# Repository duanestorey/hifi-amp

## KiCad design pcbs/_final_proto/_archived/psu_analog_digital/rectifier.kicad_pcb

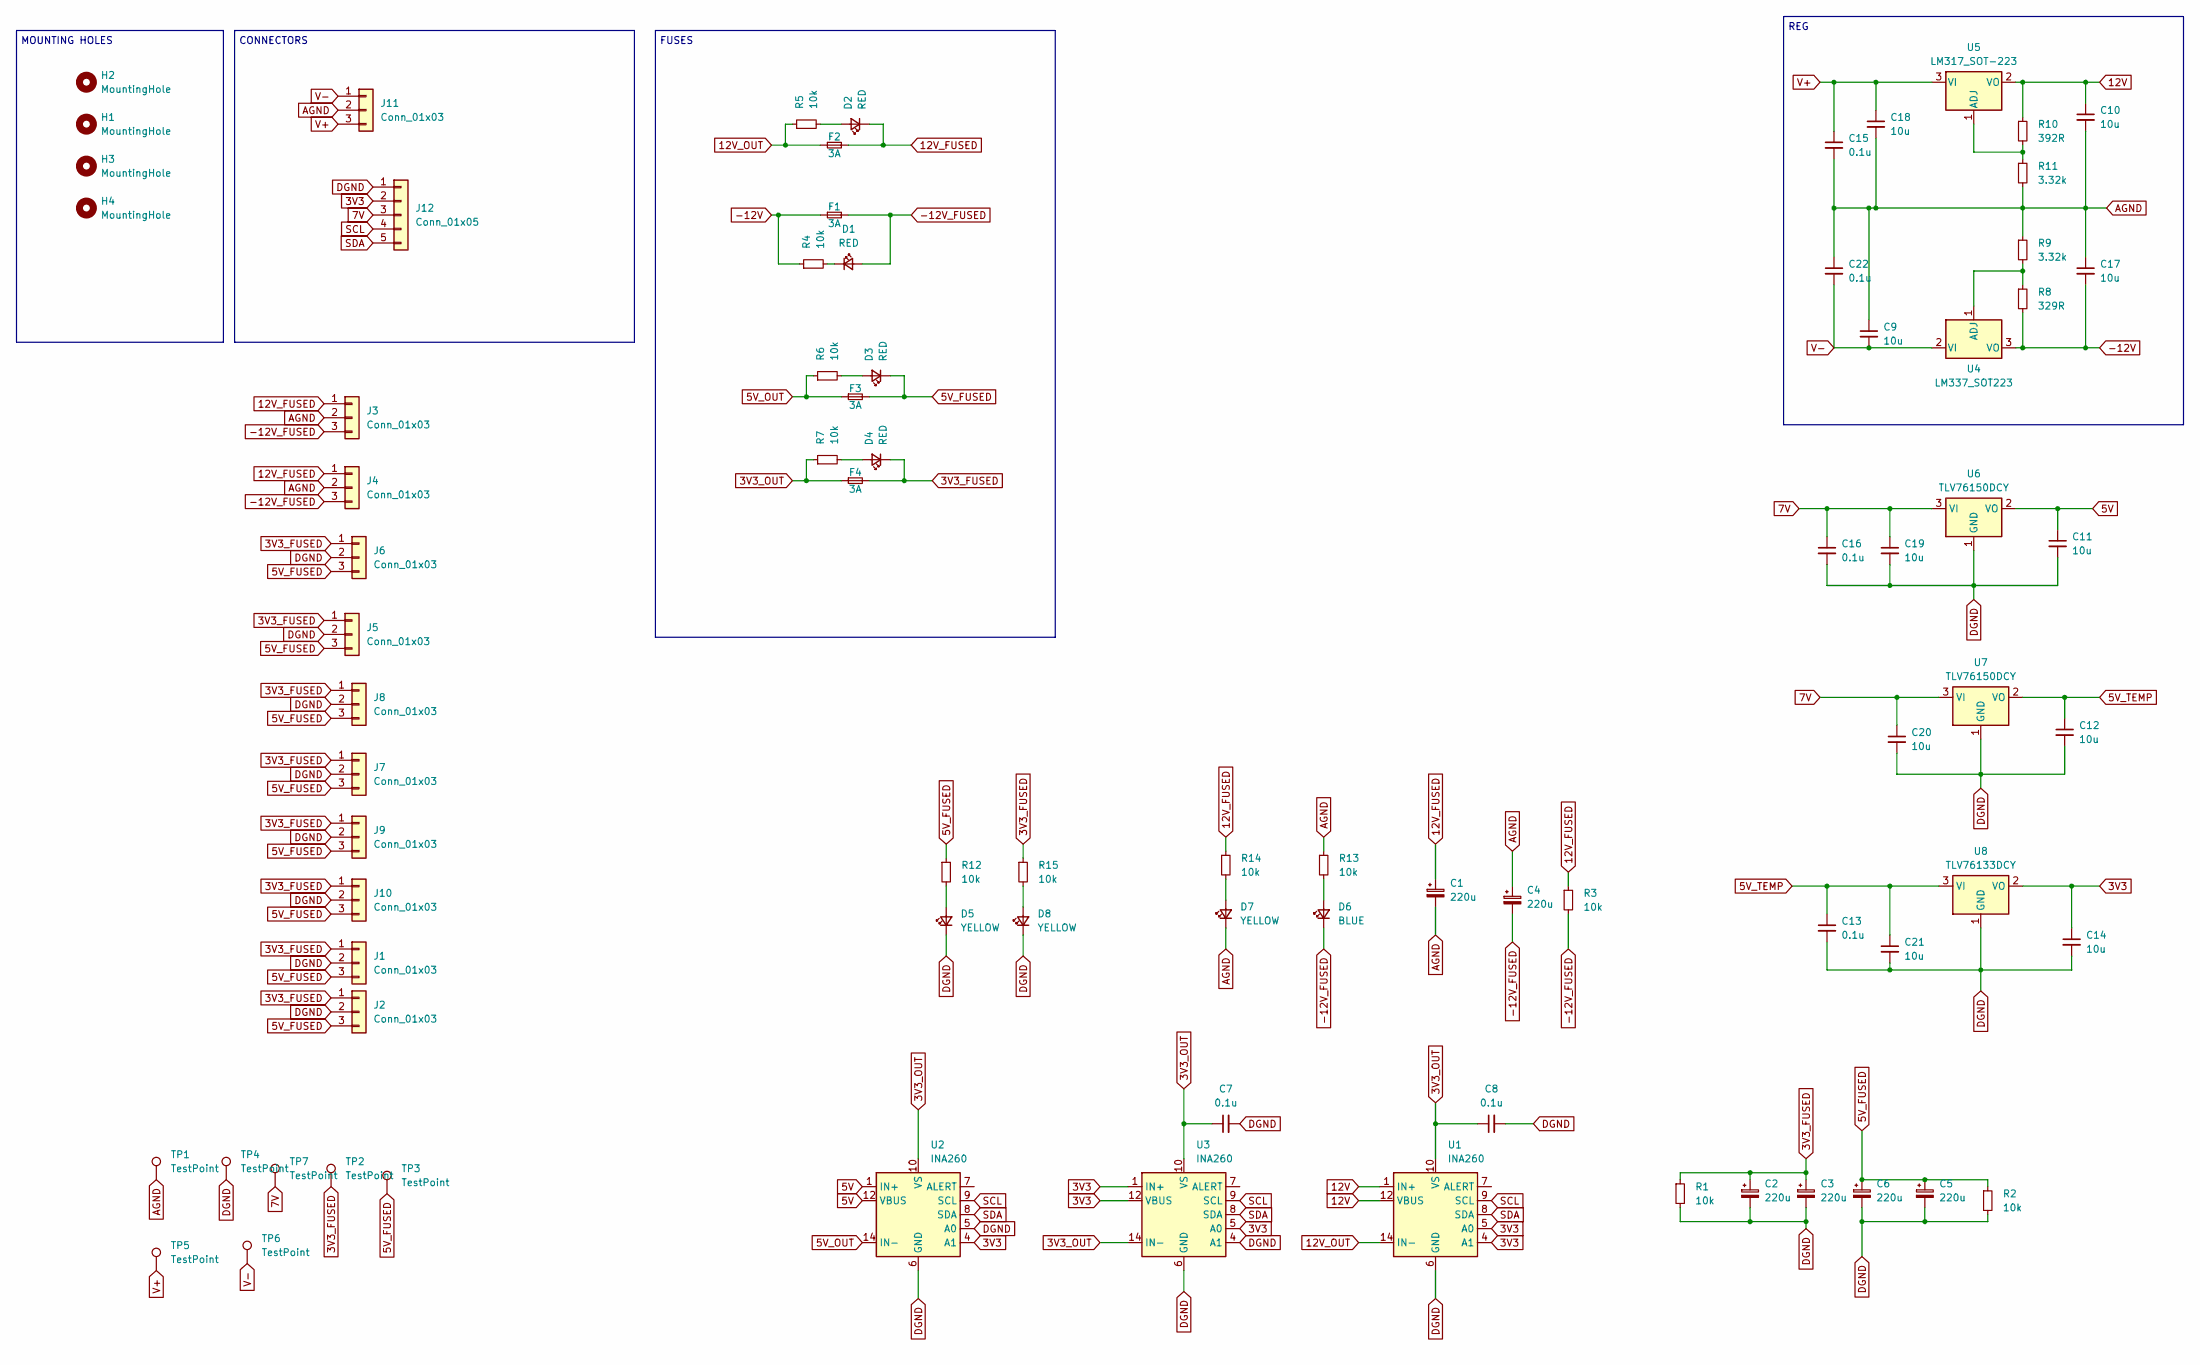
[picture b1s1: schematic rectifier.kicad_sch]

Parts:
C1, C2, C3, C4, C5, C6: 220u; CP_Radial_D6.3mm_P2.50mm
C7, C8, C13, C15, C16, C22: 0.1u; C_0805_2012Metric_Pad1.18x1.45mm_HandSolder
C9, C10, C11, C12, C14, C17, C18, C19, C20, C21: 10u; C_1206_3216Metric_Pad1.33x1.80mm_HandSolder
D1, D2, D3, D4: RED; LED_0805_2012Metric_Pad1.15x1.40mm_HandSolder
D5, D7, D8: YELLOW; LED_0805_2012Metric_Pad1.15x1.40mm_HandSolder
D6: BLUE; LED_0805_2012Metric_Pad1.15x1.40mm_HandSolder
F1, F2, F3, F4: 3A; Fuse_1812_AliExpress
H1, H2, H3, H4: MountingHole; MountingHole_3.2mm_M3_DIN965_Pad_TopBottom
J1, J2, J3, J4, J5, J6, J7, J8, J9, J10, J11: Conn_01x03; JST_PH_B3B-PH-K_1x03_P2.00mm_Vertical
J12: Conn_01x05; JST_PH_B5B-PH-K_1x05_P2.00mm_Vertical
R1, R2, R3, R4, R5, R6, R7, R12, R13, R14, R15: 10k; R_0805_2012Metric_Pad1.20x1.40mm_HandSolder; Mouser 603-SR2512JK-7W10RL
R8: 329R; R_0805_2012Metric_Pad1.20x1.40mm_HandSolder; Mouser 652-CR0805FX-3920ELF
R9, R11: 3.32k; R_0805_2012Metric_Pad1.20x1.40mm_HandSolder; Mouser AC0805FR-073K32L
R10: 392R; R_0805_2012Metric_Pad1.20x1.40mm_HandSolder; Mouser 652-CR0805FX-3920ELF
TP1, TP2, TP3, TP4, TP5, TP6, TP7: TestPoint; TestPoint_THTPad_1.5x1.5mm_Drill0.7mm
U1, U2, U3: INA260; TSSOP-16_4.4x5mm_P0.65mm
U4: LM337_SOT223; SOT-223-3_TabPin2
U5: LM317_SOT-223; SOT-223-3_TabPin2
U6, U7: TLV76150DCY; SOT-223-3_TabPin2
U8: TLV76133DCY; SOT-223-3_TabPin2

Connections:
3V3: C14.1, J12.2, U1.4 (A1), U1.5 (A0), U2.4 (A1), U3.1 (IN+), U3.2 (IN+), U3.3 (IN+), U3.5 (A0), U3.12 (VBUS), U8.2 (VO)
3V3_FUSED: C2.1, C3.1, D4.1 (K), F4.2, J1.1, J2.1, J5.1, J6.1, J7.1, J8.1, J9.1, J10.1, R1.1, R15.1, TP2.1
3V3_OUT: C7.1, C8.1, F4.1, R7.1, U1.10 (VS), U2.10 (VS), U3.10 (VS), U3.14 (IN-), U3.15 (IN-), U3.16 (IN-)
5V: C11.1, U2.1 (IN+), U2.2 (IN+), U2.3 (IN+), U2.12 (VBUS), U6.2 (VO)
5V_FUSED: C5.1, C6.1, D3.1 (K), F3.2, J1.3, J2.3, J5.3, J6.3, J7.3, J8.3, J9.3, J10.3, R2.1, R12.1, TP3.1
5V_OUT: F3.1, R6.1, U2.14 (IN-), U2.15 (IN-), U2.16 (IN-)
5V_TEMP: C12.1, C13.1, C21.1, U7.2 (VO), U8.3 (VI)
7V: C16.1, C19.1, C20.1, J12.3, TP7.1, U6.3 (VI), U7.3 (VI)
12V: C10.1, R10.1, U1.1 (IN+), U1.2 (IN+), U1.3 (IN+), U1.12 (VBUS), U5.2 (VO)
12V_FUSED: C1.1, D2.1 (K), F2.2, J3.1, J4.1, R3.1, R14.1
12V_OUT: F2.1, R5.1, U1.14 (IN-), U1.15 (IN-), U1.16 (IN-)
-12V: C17.2, F1.1, R4.1, R8.2, U4.3 (VO)
-12V_FUSED: C4.2, D1.2 (A), D6.1 (K), F1.2, J3.3, J4.3, R3.2
AGND: C1.2, C4.1, C9.1, C10.2, C15.2, C17.1, C18.2, C22.1, D7.1 (K), J3.2, J4.2, J11.2, R9.1, R11.2, R13.1, TP1.1
DGND: C2.2, C3.2, C5.2, C6.2, C7.2, C8.2, C11.2, C12.2, C13.2, C14.2, C16.2, C19.2, C20.2, C21.2, D5.1 (K), D8.1 (K), J1.2, J2.2, J5.2, J6.2, J7.2, J8.2, J9.2, J10.2, J12.1, R1.2, R2.2, TP4.1, U1.6 (GND), U1.11 (GND), U2.5 (A0), U2.6 (GND), U2.11 (GND), U3.4 (A1), U3.6 (GND), U3.11 (GND), U6.1 (GND), U7.1 (GND), U8.1 (GND)
unnamed: D1.1 (K), R4.2
unnamed: D2.2 (A), R5.2
unnamed: D3.2 (A), R6.2
unnamed: D4.2 (A), R7.2
unnamed: D5.2 (A), R12.2
unnamed: D6.2 (A), R13.2
unnamed: D7.2 (A), R14.2
unnamed: D8.2 (A), R15.2
unnamed: R8.1, R9.2, U4.1 (ADJ)
unnamed: R10.2, R11.1, U5.1 (ADJ)
SCL: J12.4, U1.9 (SCL), U2.9 (SCL), U3.9 (SCL)
SDA: J12.5, U1.8 (SDA), U2.8 (SDA), U3.8 (SDA)
V+: C15.1, C18.1, J11.3, TP5.1, U5.3 (VI)
V-: C9.2, C22.2, J11.1, TP6.1, U4.2 (VI)

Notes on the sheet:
MOUNTING HOLES
REG
CONNECTORS
FUSES

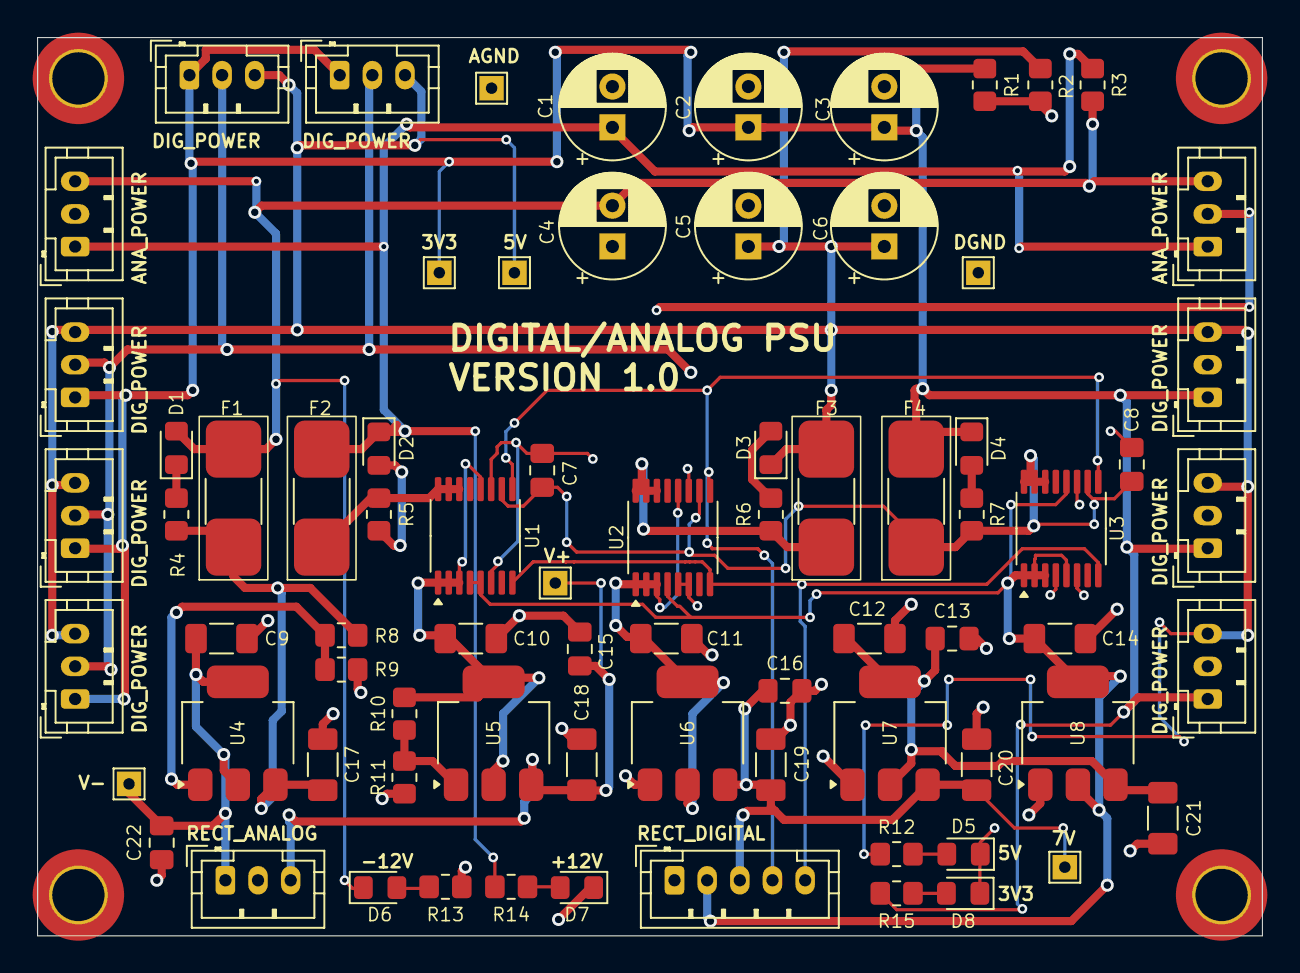
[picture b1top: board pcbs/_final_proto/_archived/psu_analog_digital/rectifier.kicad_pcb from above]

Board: 2 copper layers, 75.0 x 55.0 mm, 80 parts (0 on the bottom side), 29 nets.

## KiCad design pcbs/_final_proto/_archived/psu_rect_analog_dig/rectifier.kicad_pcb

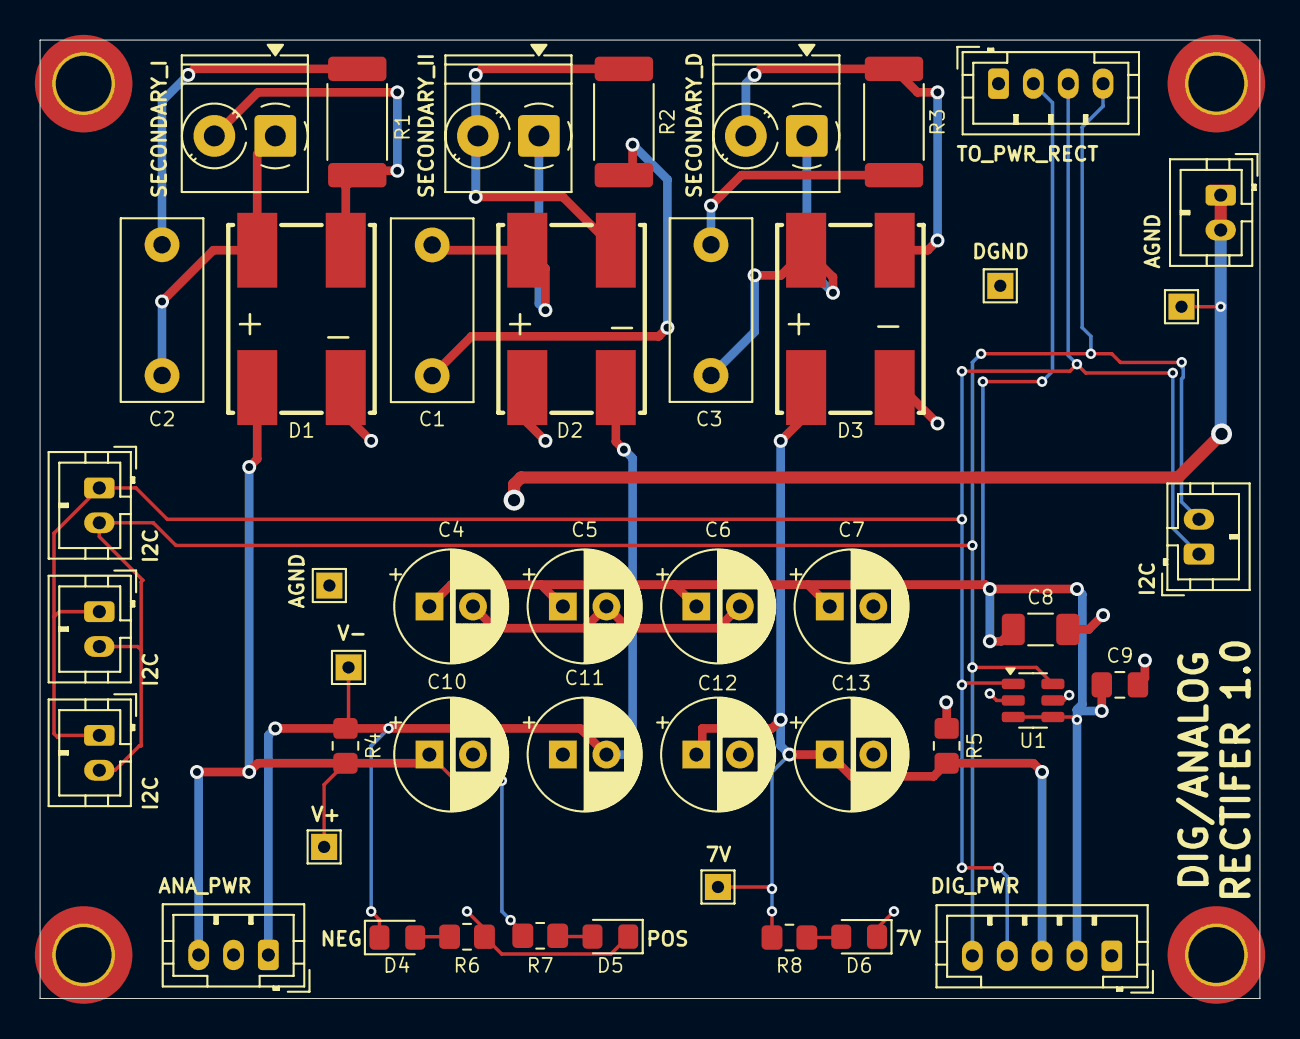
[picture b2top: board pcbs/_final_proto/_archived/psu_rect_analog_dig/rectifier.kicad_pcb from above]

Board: 2 copper layers, 70.0 x 55.0 mm, 49 parts (0 on the bottom side), 20 nets.

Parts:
C1, C2, C3: 100N; C_Rect_L10.3mm_W4.5mm_P7.50mm_MKS4
C4, C5, C6, C7, C10, C11, C12, C13: 220u; CP_Radial_D6.3mm_P2.50mm
C8: 10u; C_1206_3216Metric_Pad1.33x1.80mm_HandSolder
C9: 0.1u; C_0805_2012Metric_Pad1.18x1.45mm_HandSolder
D1, D2, D3: CD-DF406SL; Z4-D_4P-L10.5-W8.1-P5.08-TL
D4: BLUE; LED_0805_2012Metric_Pad1.15x1.40mm_HandSolder
D5, D6: YELLOW; LED_0805_2012Metric_Pad1.15x1.40mm_HandSolder
H1, H2, H3, H4: MountingHole; MountingHole_3.2mm_M3_DIN965_Pad_TopBottom
J1: Conn_01x04; JST_PH_B4B-PH-K_1x04_P2.00mm_Vertical
J2, J3, J4: Conn_01x02; TerminalBlock_Phoenix_PT-1,5-2-3.5-H_1x02_P3.50mm_Horizontal
J5, J6, J9, J10, J11: Conn_01x02; JST_PH_B2B-PH-K_1x02_P2.00mm_Vertical
J7: Conn_01x03; JST_PH_B3B-PH-K_1x03_P2.00mm_Vertical
J8: Conn_01x05; JST_PH_B5B-PH-K_1x05_P2.00mm_Vertical
R1, R2, R3: 10R 2W; R_2512_6332Metric_Pad1.40x3.35mm_HandSolder
R4, R5: 100k; R_0805_2012Metric_Pad1.20x1.40mm_HandSolder
R6, R7, R8: 10k; R_0805_2012Metric_Pad1.20x1.40mm_HandSolder
TP1, TP2, TP3, TP4, TP5, TP6: TestPoint; TestPoint_THTPad_1.5x1.5mm_Drill0.7mm
U1: TMP100; SOT-23-6

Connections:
3V3: C4.1, C5.1, C6.1, C7.1, C8.1, C9.1, J1.2, J8.2, U1.3 (ADD1), U1.4 (V+)
7V: C12.1, C13.1, D3.1 (+), J8.3, R5.1, R8.1, TP3.1
AGND: C10.2, C11.1, D1.4 (-), D2.1 (+), D5.1 (K), J7.2, J9.1, J9.2, R6.1, TP5.1, TP6.1
DGND: C4.2, C5.2, C6.2, C7.2, C8.2, C9.2, C12.2, C13.2, D3.4 (-), D6.1 (K), J1.1, J8.1, R5.2, TP4.1, U1.2 (GND), U1.5 (ADD0)
unnamed: C1.2, R2.1
unnamed: C2.2, R1.1
unnamed: C3.2, R3.1
unnamed: D4.2 (A), R6.2
unnamed: D5.2 (A), R7.2
unnamed: D6.2 (A), R8.2
SCL: J1.3, J5.1, J6.1, J8.4, J10.1, J11.1, U1.1 (SCL)
SDA: J1.4, J5.2, J6.2, J8.5, J10.2, J11.2, U1.6 (SDA)
SEC_1_NEG: D1.3 (AC), J2.2, R1.2
SEC_1_POS: C2.1, D1.2 (AC), J2.1
SEC_2_NEG: D2.3 (AC), J3.2, R2.2
SEC_2_POS: C1.1, D2.2 (AC), J3.1
SEC_3_NEG: D3.3 (AC), J4.2, R3.2
SEC_3_POS: C3.1, D3.2 (AC), J4.1
V+: C10.1, D1.1 (+), J7.3, R4.1, R7.1, TP2.1
V-: C11.2, D2.4 (-), D4.1 (K), J7.1, R4.2, TP1.1

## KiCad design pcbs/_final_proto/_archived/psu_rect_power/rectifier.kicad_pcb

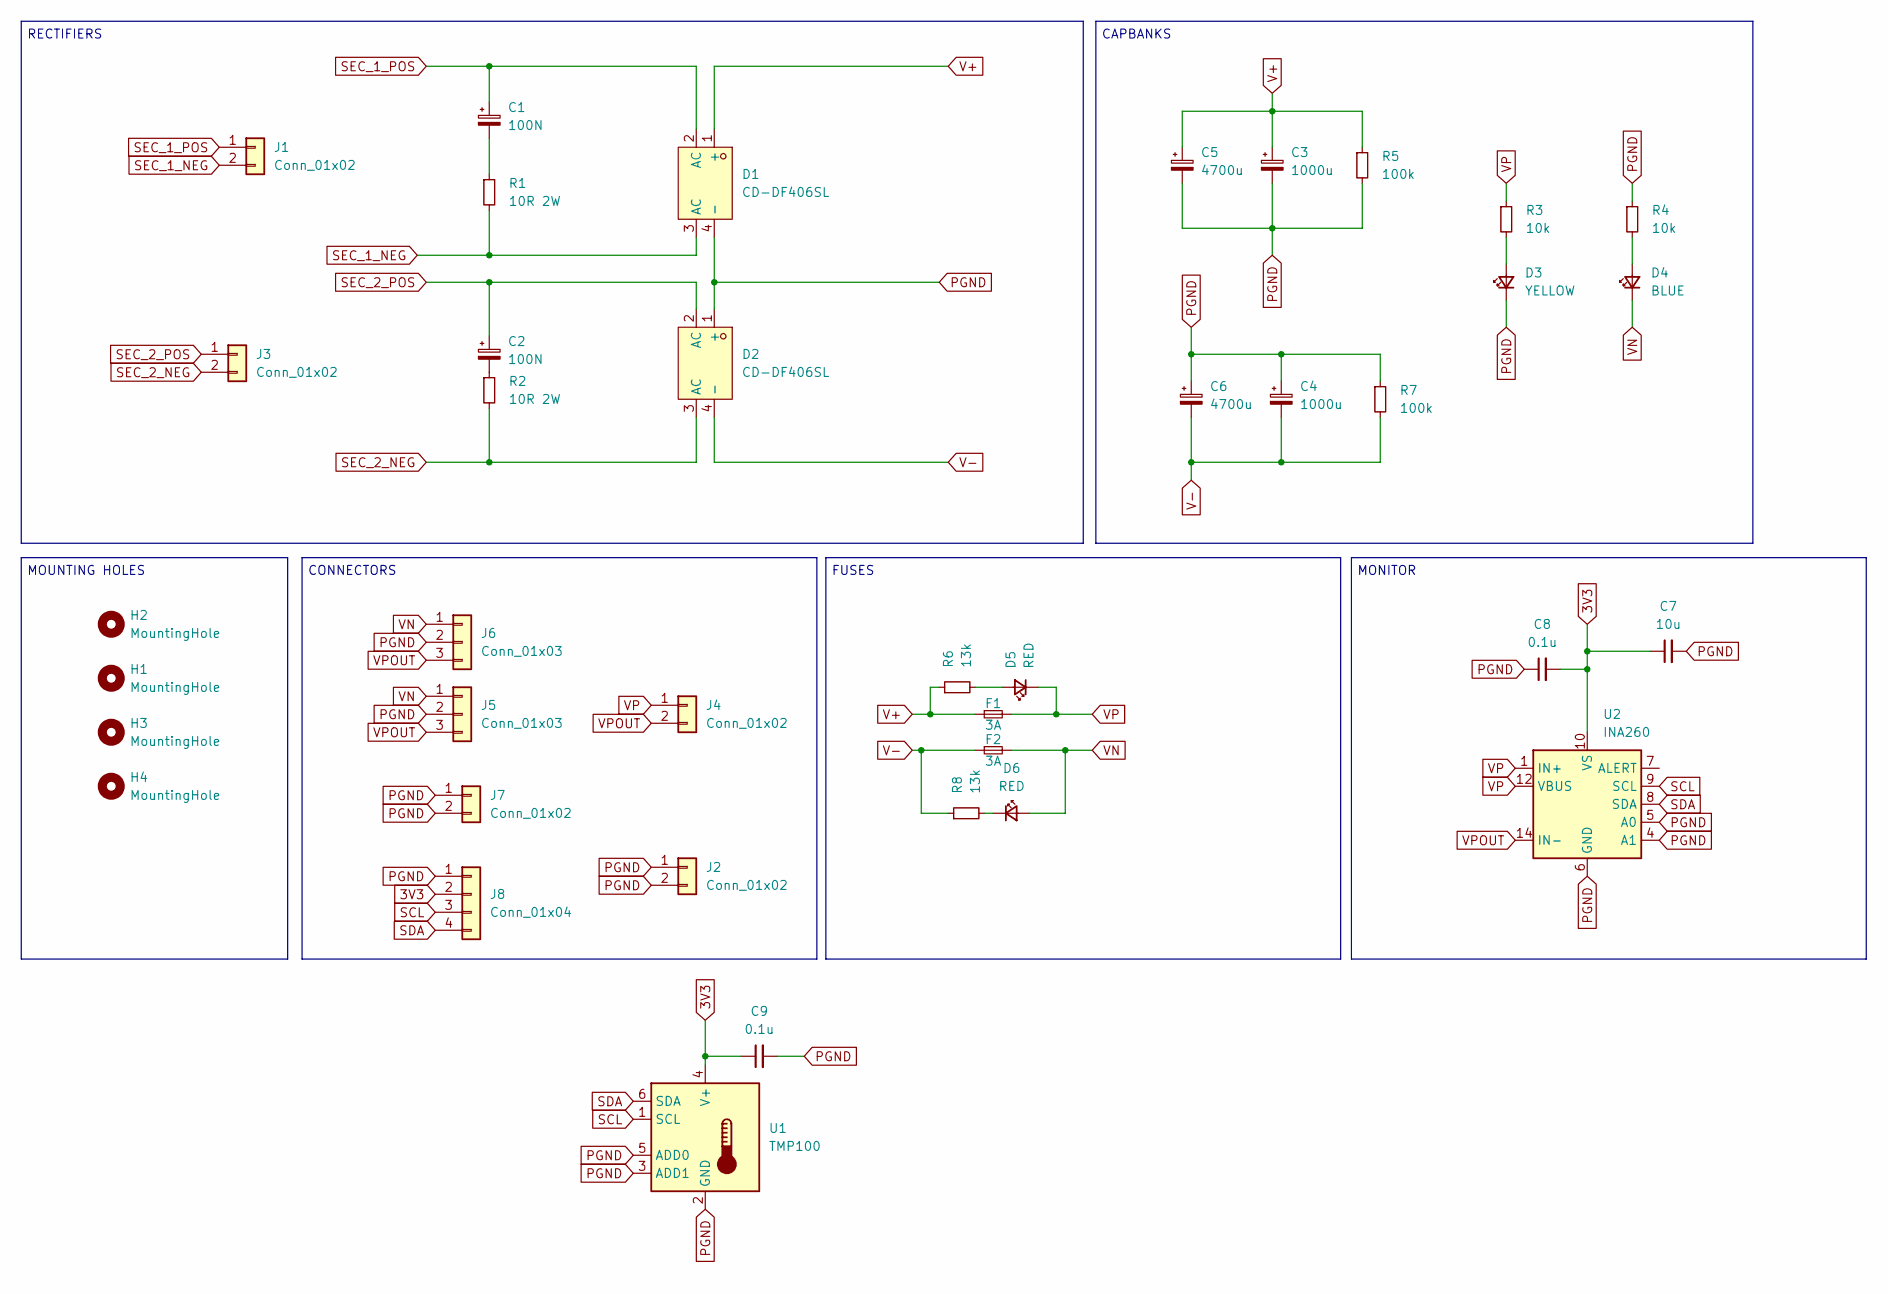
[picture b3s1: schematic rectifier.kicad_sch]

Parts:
C1, C2: 100N; C_Rect_L10.3mm_W4.5mm_P7.50mm_MKS4; Mouser MKP4F031002D00KF00
C3, C4: 1000u; CP_Radial_D12.5mm_P5.00mm
C5, C6: 4700u; CP_Radial_D18.0mm_P7.50mm
C7: 10u; C_1206_3216Metric_Pad1.33x1.80mm_HandSolder
C8, C9: 0.1u; C_0805_2012Metric_Pad1.18x1.45mm_HandSolder_Duane
D1, D2: CD-DF406SL; Z4-D_4P-L10.5-W8.1-P5.08-TL; LCSC Part C17188088
D3: YELLOW; LED_0805_2012Metric_Pad1.15x1.40mm_HandSolder
D4: BLUE; LED_0805_2012Metric_Pad1.15x1.40mm_HandSolder
D5, D6: RED; LED_0805_2012Metric_Pad1.15x1.40mm_HandSolder
F1, F2: 3A; Fuse_1812_AliExpress
H1, H2, H3, H4: MountingHole; MountingHole_3.2mm_M3_DIN965_Pad_TopBottom
J1, J2, J3: Conn_01x02; TerminalBlock_Phoenix_PT-1,5-2-3.5-H_1x02_P3.50mm_Horizontal
J4: Conn_01x02; PinHeader_1x02_P2.54mm_Vertical
J5, J6: Conn_01x03; JST_VH_B3P-VH_1x03_P3.96mm_Vertical
J7: Conn_01x02; JST_PH_B2B-PH-K_1x02_P2.00mm_Vertical
J8: Conn_01x04; JST_PH_B4B-PH-K_1x04_P2.00mm_Vertical
R1, R2: 10R 2W; R_2512_6332Metric_Pad1.40x3.35mm_HandSolder; Mouser 603-SR2512JK-7W10RL
R3, R4: 10k; R_0805_2012Metric_Pad1.20x1.40mm_HandSolder; Mouser 603-SR2512JK-7W10RL
R5, R7: 100k; R_0805_2012Metric_Pad1.20x1.40mm_HandSolder; Mouser 603-SR2512JK-7W10RL
R6, R8: 13k; R_0805_2012Metric_Pad1.20x1.40mm_HandSolder; Mouser 603-SR2512JK-7W10RL
U1: TMP100; SOT-23-6
U2: INA260; TSSOP-16_4.4x5mm_P0.65mm

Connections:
3V3: C7.1, C8.2, C9.1, J8.2, U1.4 (V+), U2.10 (VS)
unnamed: C1.2, R1.1
unnamed: C2.2, R2.1
unnamed: D3.2 (A), R3.2
unnamed: D4.2 (A), R4.2
unnamed: D5.2 (A), R6.2
unnamed: D6.1 (K), R8.2
PGND: C3.2, C4.1, C5.2, C6.1, C7.2, C8.1, C9.2, D1.4 (-), D2.1 (+), D3.1 (K), J2.1, J2.2, J5.2, J6.2, J7.1, J7.2, J8.1, R4.1, R5.2, R7.1, U1.2 (GND), U1.3 (ADD1), U1.5 (ADD0), U2.4 (A1), U2.5 (A0), U2.6 (GND), U2.11 (GND)
SCL: J8.3, U1.1 (SCL), U2.9 (SCL)
SDA: J8.4, U1.6 (SDA), U2.8 (SDA)
SEC_1_NEG: D1.3 (AC), J1.2, R1.2
SEC_1_POS: C1.1, D1.2 (AC), J1.1
SEC_2_NEG: D2.3 (AC), J3.2, R2.2
SEC_2_POS: C2.1, D2.2 (AC), J3.1
V+: C3.1, C5.1, D1.1 (+), F1.1, R5.1, R6.1
V-: C4.2, C6.2, D2.4 (-), F2.1, R7.2, R8.1
VN: D4.1 (K), D6.2 (A), F2.2, J5.1, J6.1
VP: D5.1 (K), F1.2, J4.1, R3.1, U2.1 (IN+), U2.2 (IN+), U2.3 (IN+), U2.12 (VBUS)
VPOUT: J4.2, J5.3, J6.3, U2.14 (IN-), U2.15 (IN-), U2.16 (IN-)

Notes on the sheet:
MOUNTING HOLES
MONITOR
CONNECTORS
RECTIFIERS
CAPBANKS
FUSES

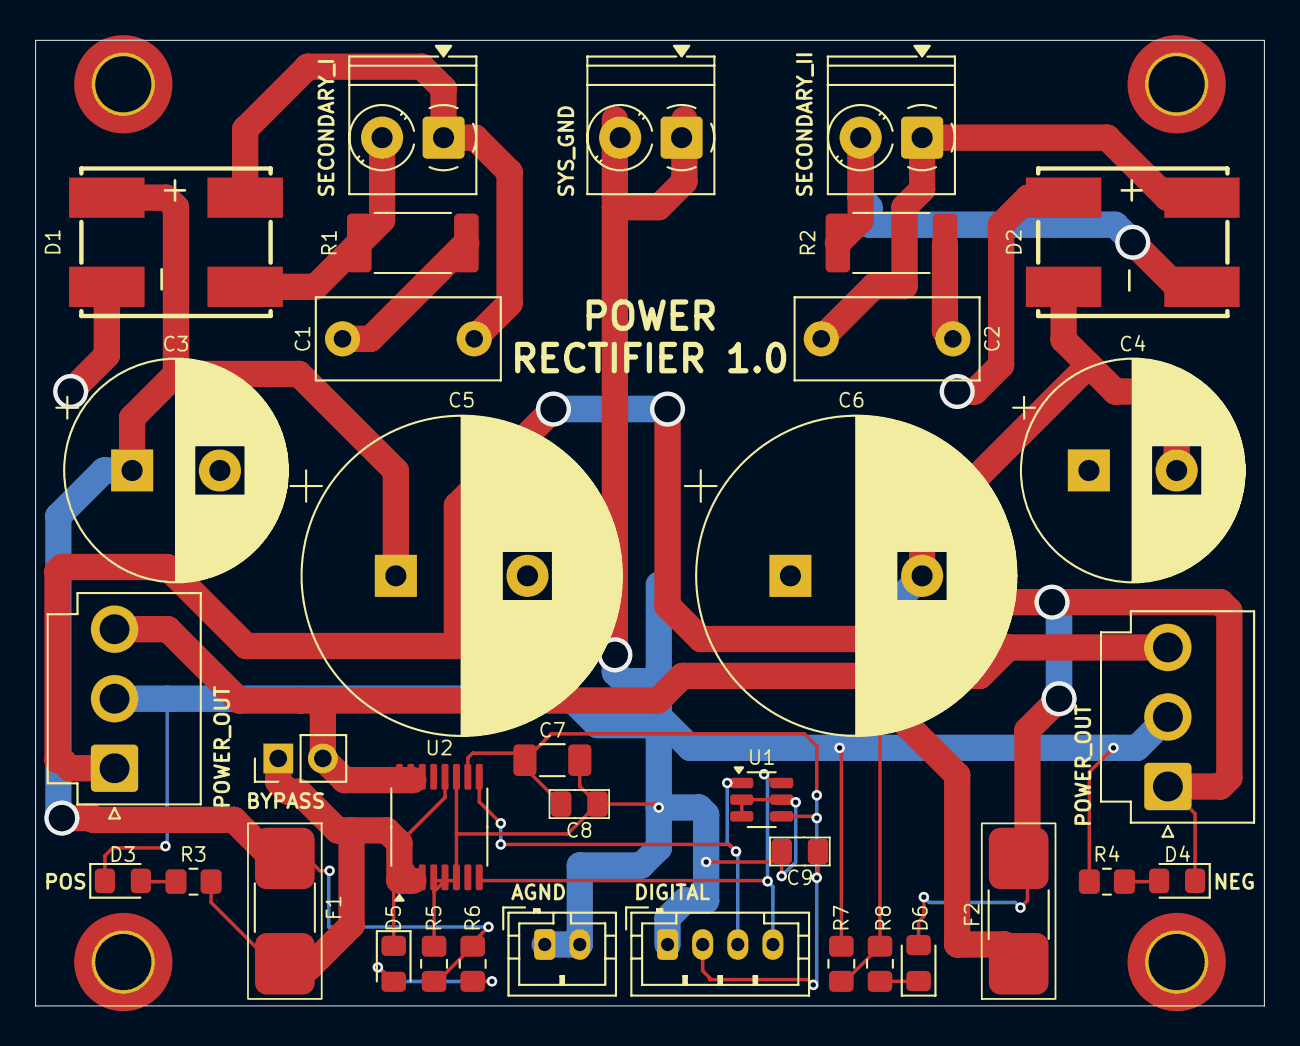
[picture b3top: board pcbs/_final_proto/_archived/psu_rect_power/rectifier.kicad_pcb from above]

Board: 2 copper layers, 70.0 x 55.0 mm, 39 parts (0 on the bottom side), 19 nets.

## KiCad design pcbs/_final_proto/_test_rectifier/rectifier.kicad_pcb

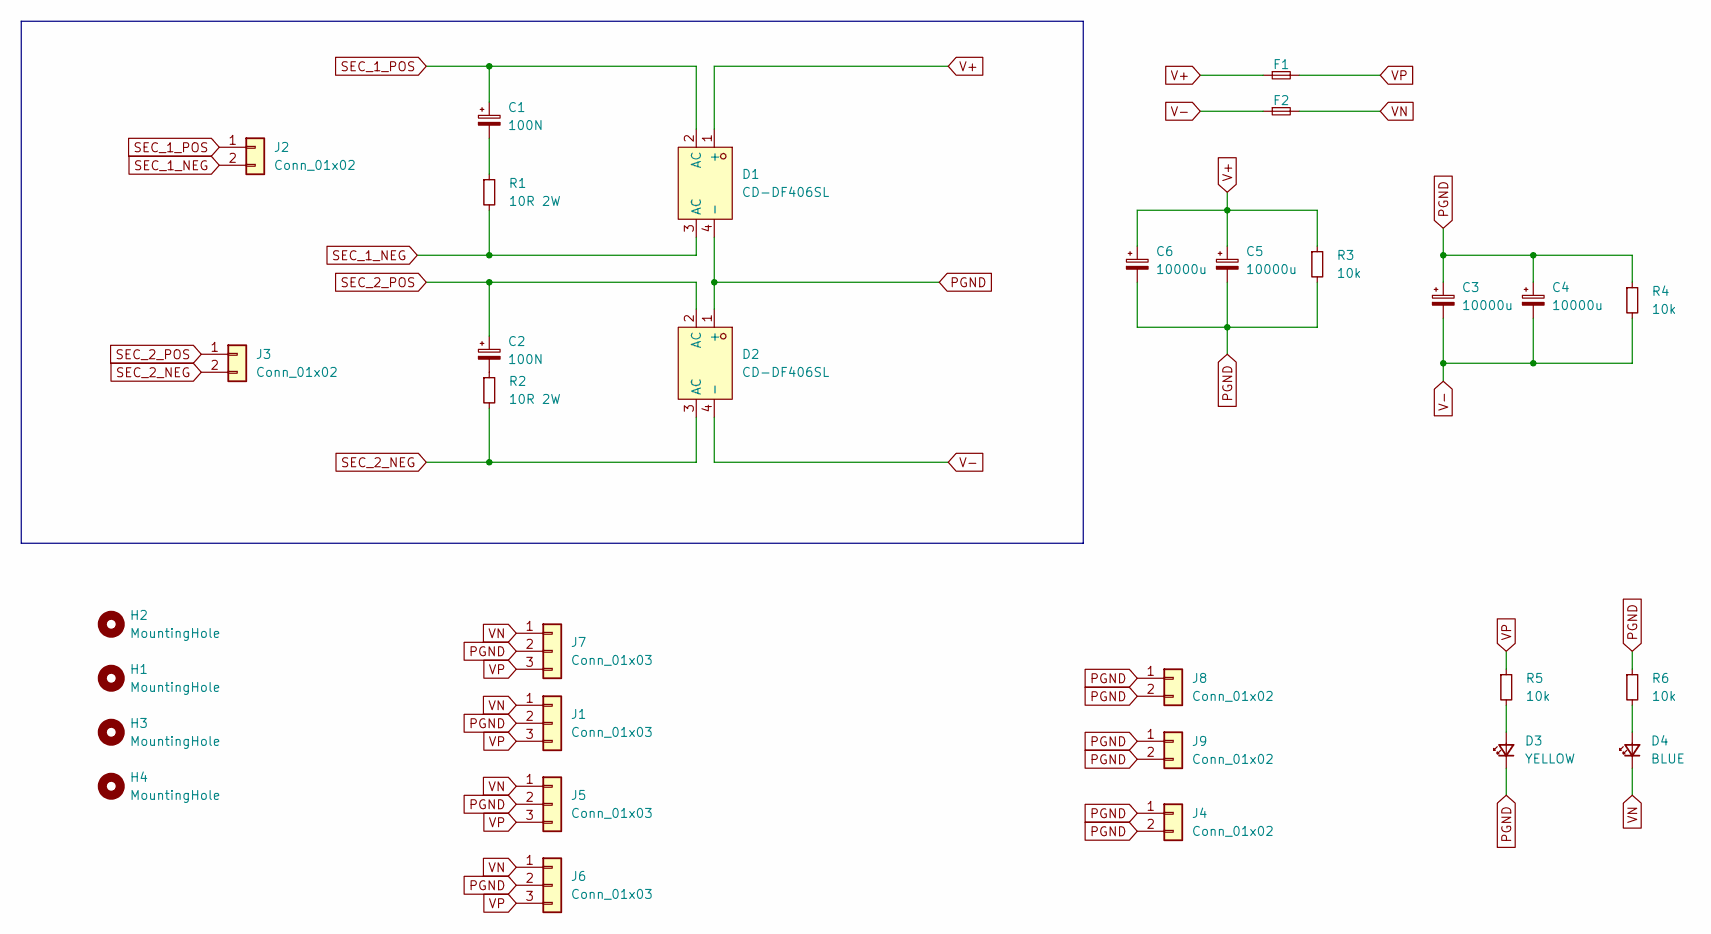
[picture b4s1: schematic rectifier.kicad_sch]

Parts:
C1, C2: 100N; C_Rect_L10.3mm_W4.5mm_P7.50mm_MKS4; Mouser MKP4F031002D00KF00
C3, C4, C5, C6: 10000u; CP_Radial_D18.0mm_P7.50mm
D1, D2: CD-DF406SL; Z4-D_4P-L10.5-W8.1-P5.08-TL; LCSC Part C17188088
D3: YELLOW; LED_0805_2012Metric_Pad1.15x1.40mm_HandSolder
D4: BLUE; LED_0805_2012Metric_Pad1.15x1.40mm_HandSolder
F1, F2: Fuse_Small; Aliexpress Fuse 5x20
H1, H2, H3, H4: MountingHole; MountingHole_3.2mm_M3_DIN965_Pad_TopBottom
J1, J5, J6, J7: Conn_01x03; TerminalBlock_Phoenix_PT-1,5-3-5.0-H_1x03_P5.00mm_Horizontal
J2, J3: Conn_01x02; TerminalBlock_Phoenix_MKDS-1,5-2_1x02_P5.00mm_Horizontal
J4, J8, J9: Conn_01x02; JST_VH_B2P-VH-B_1x02_P3.96mm_Vertical
R1, R2: 10R 2W; R_2512_6332Metric_Pad1.40x3.35mm_HandSolder; Mouser 603-SR2512JK-7W10RL
R3, R4, R5, R6: 10k; R_0805_2012Metric_Pad1.20x1.40mm_HandSolder; Mouser 603-SR2512JK-7W10RL

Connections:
unnamed: C1.2, R1.1
unnamed: C2.2, R2.1
unnamed: D3.2 (A), R5.2
unnamed: D4.2 (A), R6.2
PGND: C3.1, C4.1, C5.2, C6.2, D1.4 (-), D2.1 (+), D3.1 (K), J1.2, J4.1, J4.2, J5.2, J6.2, J7.2, J8.1, J8.2, J9.1, J9.2, R3.2, R4.1, R6.1
SEC_1_NEG: D1.3 (AC), J2.2, R1.2
SEC_1_POS: C1.1, D1.2 (AC), J2.1
SEC_2_NEG: D2.3 (AC), J3.2, R2.2
SEC_2_POS: C2.1, D2.2 (AC), J3.1
V+: C5.1, C6.1, D1.1 (+), F1.1, R3.1
V-: C3.2, C4.2, D2.4 (-), F2.1, R4.2
VN: D4.1 (K), F2.2, J1.1, J5.1, J6.1, J7.1
VP: F1.2, J1.3, J5.3, J6.3, J7.3, R5.1

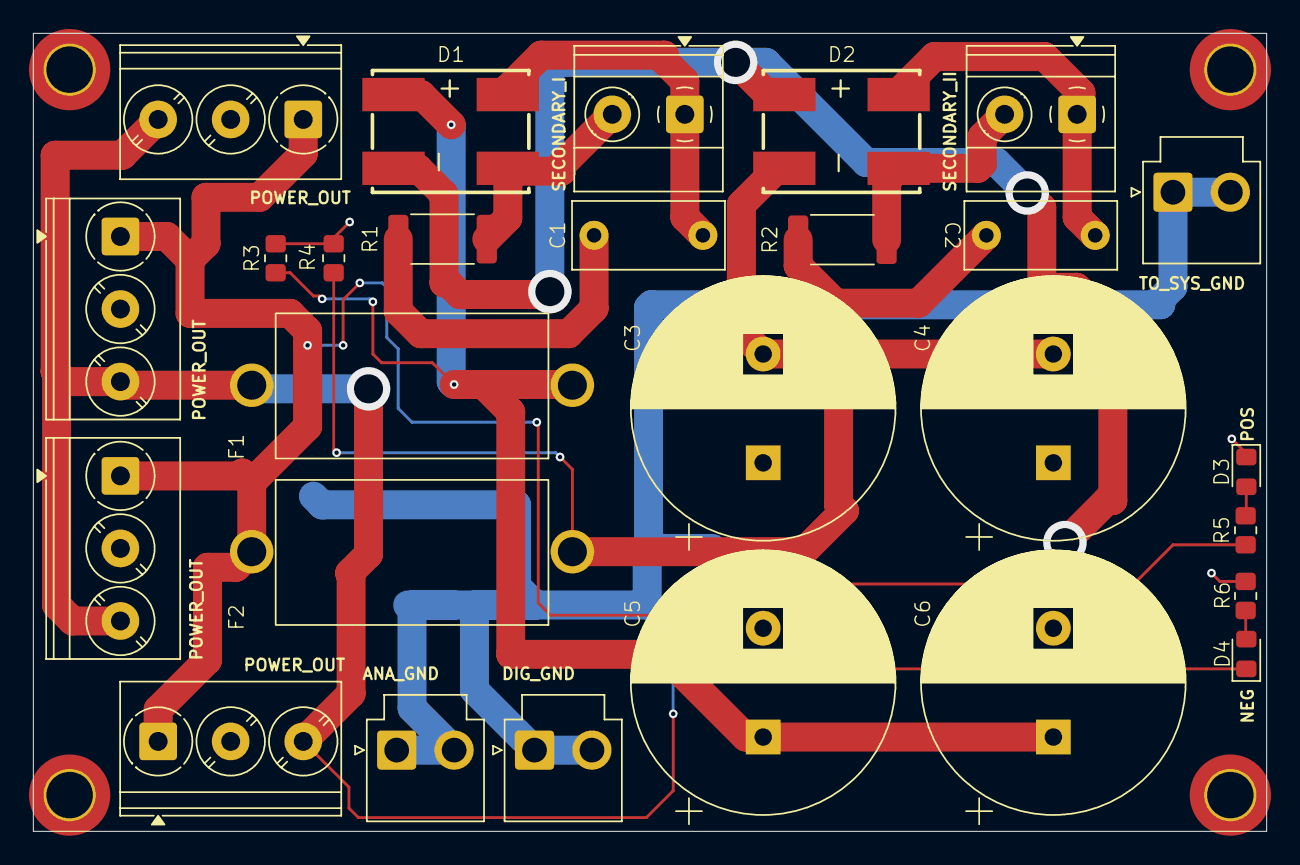
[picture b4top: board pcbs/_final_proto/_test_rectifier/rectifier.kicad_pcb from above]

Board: 2 copper layers, 85.0 x 55.0 mm, 31 parts (0 on the bottom side), 13 nets.
